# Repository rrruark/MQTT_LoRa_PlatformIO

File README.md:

# MQTT_LoRa_PlatformIO
ESP32 SX1262 LoRa to MQTT Bridge

This code is in a working state and is configured for the Heltec WiFi Lora 32 V2 Board. The only thing you need to change to get started are the WiFi and MQTT configuration parameters.

It will transmit (over LoA using an SX1262) messages posted to a MQTT topic using radio configuration parameters defined in other MQTT topics.
It will also post messages received from the SX1262 to a different MQTT topic and will re-transmit received messages allowing it to act as a repeater.

The LoRa messages are not currently compatible with The Things Network, Helium, and other commonly used LoRaWAN Internet of Shit services.

My longer term ambition is to add support for <a href="https://github.com/lora-aprs/LoRa_APRS_Tracker">LoRa APRS</a> and <a href="https://github.com/aprs434/aprs434.github.io">aprs434</a>. LoRa APRS has chosen a bandwidth and spreading factor that results in much longer transmit times than traditional AFSK1200 APRS and it does not pack messages efficiently. aprs434 proposes a more efficient packing and a higher bitrate.

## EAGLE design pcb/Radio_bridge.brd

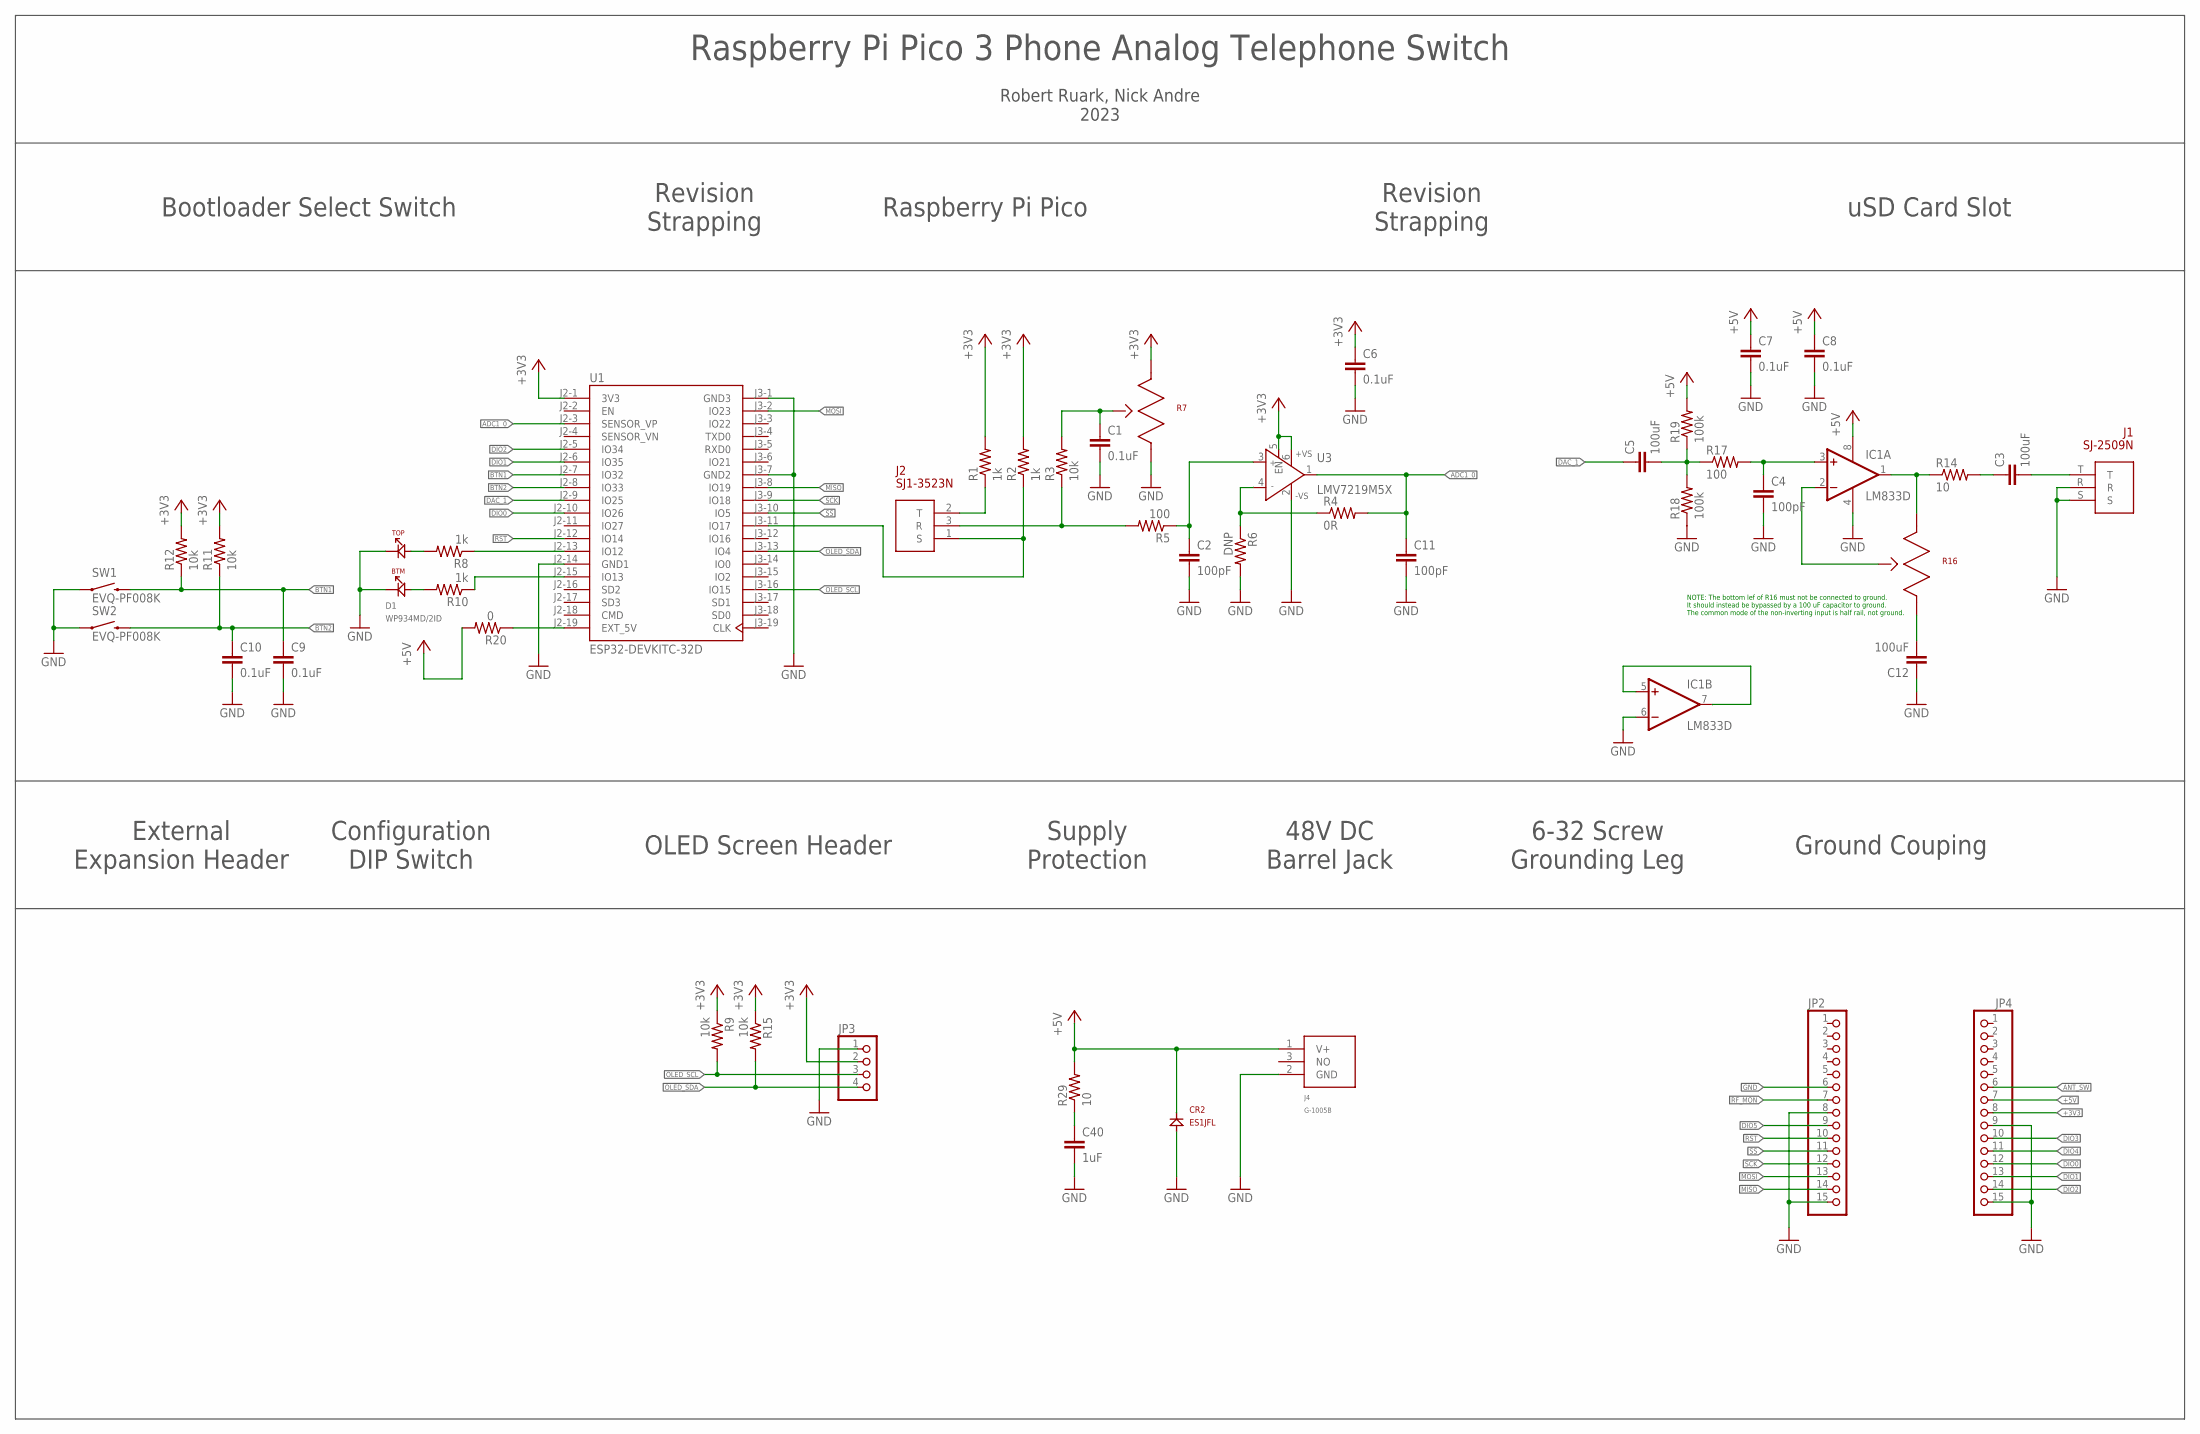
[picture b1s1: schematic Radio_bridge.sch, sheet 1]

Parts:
C1, C6, C7, C8, C9, C10: 0.1uF; 0603
C2, C4, C11: 100pF; 0603
C3, C5, C12: 100uF; 1210
C40: 1uF; 1206
CR2: ES1JFL; SOD123(AK)
D1: WP934MD/2ID
IC1: LM833D; SO08
J1: SJ-2509N; 2.5MM_TRS
J2: SJ1-3523N
J4: G-1005B
JP2, JP4: PINHD-1X15; 1X15
JP3: PINHD-1X4; 1X04
R1, R2, R8, R10: 1k; 0603
R3, R9, R11, R12, R15: 10k; 0603
R4: 0R; 0603
R5, R17: 100; 0603
R6: DNP; 0603
R7, R16: 10k; PTV09
R14: 10; 0603
R18, R19: 100k; 0603
R20: 0; 0603
R29: 10; 1206
SW1, SW2: EVQ-PF008K
U1: ESP32-DEVKITC-32D; MODULE_ESP32-DEVKITC-32D
U3: LMV7219M5X; SOT23-6

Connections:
+3V3: C6.1, JP3.2, JP4.8, R1.2, R2.2, R7.1, R9.1, R11.2, R12.2, R15.1, U1.J2-1 (3V3), U3.5 (EN), U3.6 (+VS)
+5V: C7.1, C8.1, CR2.K, IC1.8 (V+), J4.1 (V+), JP4.7, R19.2, R20.2, R29.2
ADC1_0: C11.1, R4.2, U1.J2-3 (SENSOR_VP), U3.1 (OUT)
ANT_SW: JP4.6
BTN1: C9.1, R12.1, SW1.S2 (2), U1.J2-7 (IO32)
BTN2: C10.1, R11.1, SW2.S2 (2), U1.J2-8 (IO33)
DAC_1: C5.1, U1.J2-9 (IO25)
DIO0: JP4.12, U1.J2-10 (IO26)
DIO1: JP4.13, U1.J2-6 (IO35)
DIO2: JP4.14, U1.J2-5 (IO34)
DIO3: JP4.10
DIO4: JP4.11
DIO5: JP2.9
GND: C1.2, C2.2, C4.2, C6.2, C7.2, C8.2, C9.2, C10.2, C11.2, C12.1, C40.2, CR2.A, D1.K1, D1.K2, IC1.4 (V-), IC1.6 (-IN), J1.R, J1.S, J4.2 (GND), JP2.6, JP2.8, JP2.15, JP3.1, JP4.9, JP4.15, R6.2, R7.3, R18.1, SW1.S1 (1), SW2.S1 (1), U1.J2-14 (GND1), U1.J3-1 (GND3), U1.J3-7 (GND2), U3.2 (-VS)
MIC: C2.1, R5.1, U3.3 (IN+)
MISO: JP2.14, U1.J3-8 (IO19)
MOSI: JP2.13, U1.J3-2 (IO23)
unnamed: J2.2 (T), R1.1
unnamed: C1.1, R3.2, R7.2
unnamed: R4.1, R6.1, U3.4 (IN-)
unnamed: J2.1 (S), R2.1, U1.J3-11 (IO17)
unnamed: C3.2, J1.T
unnamed: J2.3 (R), R3.1, R5.2
unnamed: D1.A2, R8.2
unnamed: D1.A1, R10.2
unnamed: R8.1, U1.J2-13 (IO12)
unnamed: R10.1, U1.J2-15 (IO13)
unnamed: C12.2, R16.3
unnamed: IC1.5 (+IN), IC1.7 (OUT)
unnamed: IC1.1 (OUT), R14.1, R16.1
unnamed: C3.1, R14.2
unnamed: IC1.2 (-IN), R16.2
unnamed: C4.1, IC1.3 (+IN), R17.2
unnamed: C5.2, R17.1, R18.2, R19.1
unnamed: R20.1, U1.J2-19 (EXT_5V)
unnamed: C40.1, R29.1
OLED_SCL: JP3.3, R9.2, U1.J3-16 (IO15)
OLED_SDA: JP3.4, R15.2, U1.J3-13 (IO4)
RF_MON: JP2.7
RST: JP2.10, U1.J2-12 (IO14)
SCK: JP2.12, U1.J3-9 (IO18)
SS: JP2.11, U1.J3-10 (IO5)

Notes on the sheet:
Raspberry Pi Pico 3 Phone Analog Telephone Switch
Robert Ruark, Nick Andre 2023
Raspberry Pi Pico
Ground Couping
External Expansion Header
OLED Screen Header
48V DC Barrel Jack
6-32 Screw Grounding Leg
Configuration DIP Switch
Supply Protection
Revision Strapping
Bootloader Select Switch
uSD Card Slot
NOTE: The bottom lef of R16 must not be connected to ground. It should instead be bypassed by a 100 uF capacitor to ground. The common mode of the non-inverting input is half rail, not ground.

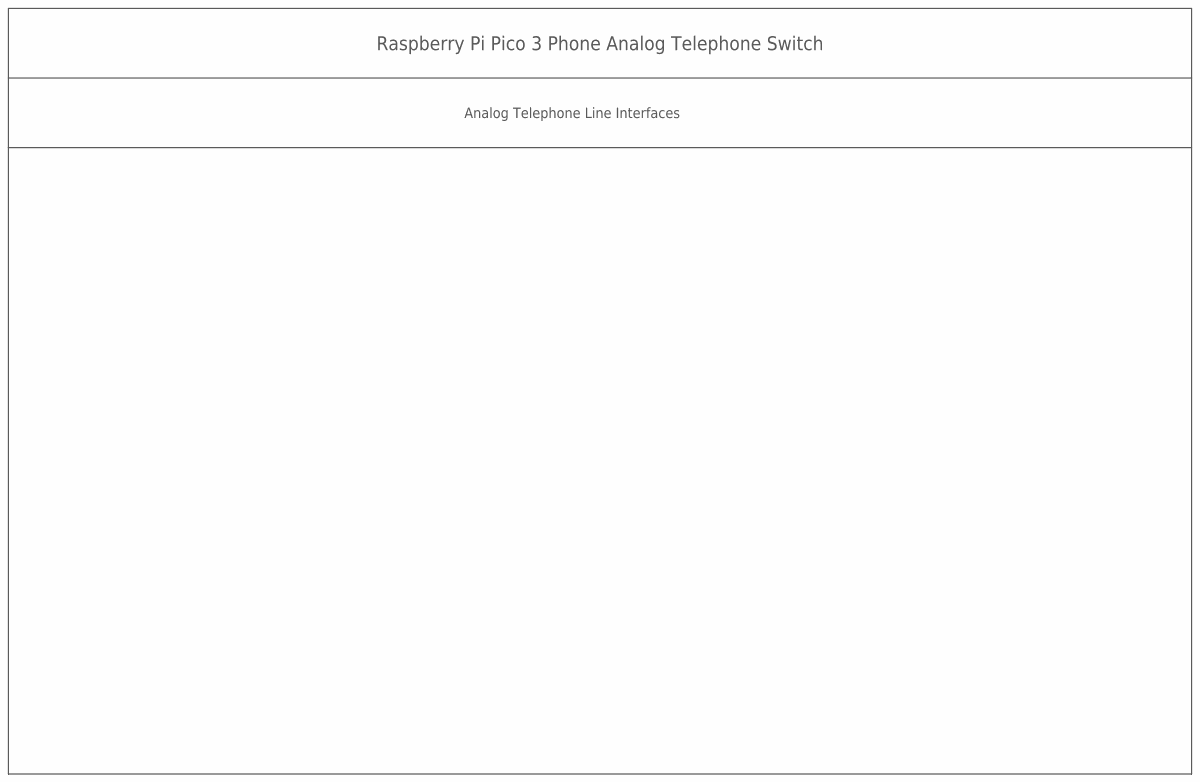
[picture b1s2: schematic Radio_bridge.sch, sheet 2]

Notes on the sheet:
Raspberry Pi Pico 3 Phone Analog Telephone Switch
Analog Telephone Line Interfaces

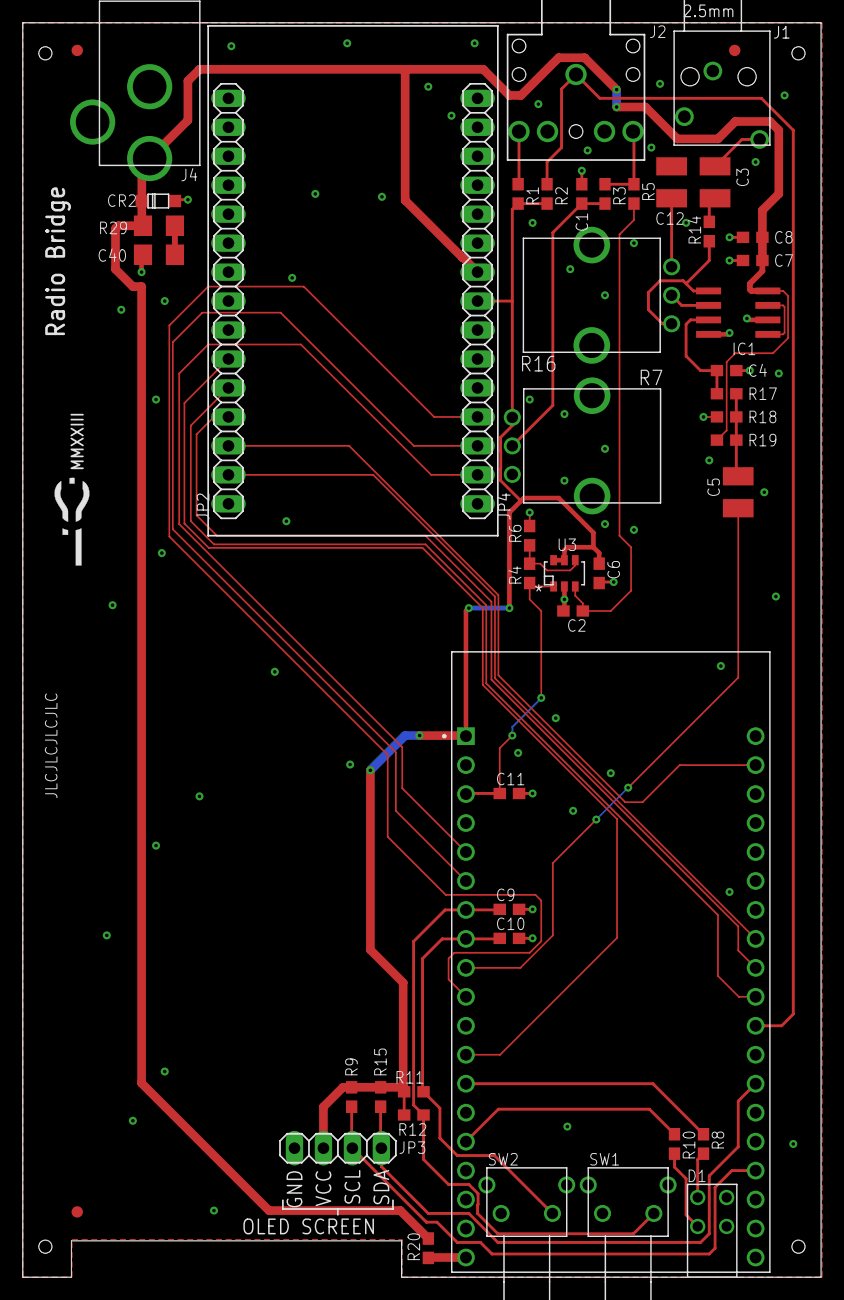
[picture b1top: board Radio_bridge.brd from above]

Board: 2 copper layers, 70.0 x 110.0 mm, 46 parts (0 on the bottom side), 37 nets.

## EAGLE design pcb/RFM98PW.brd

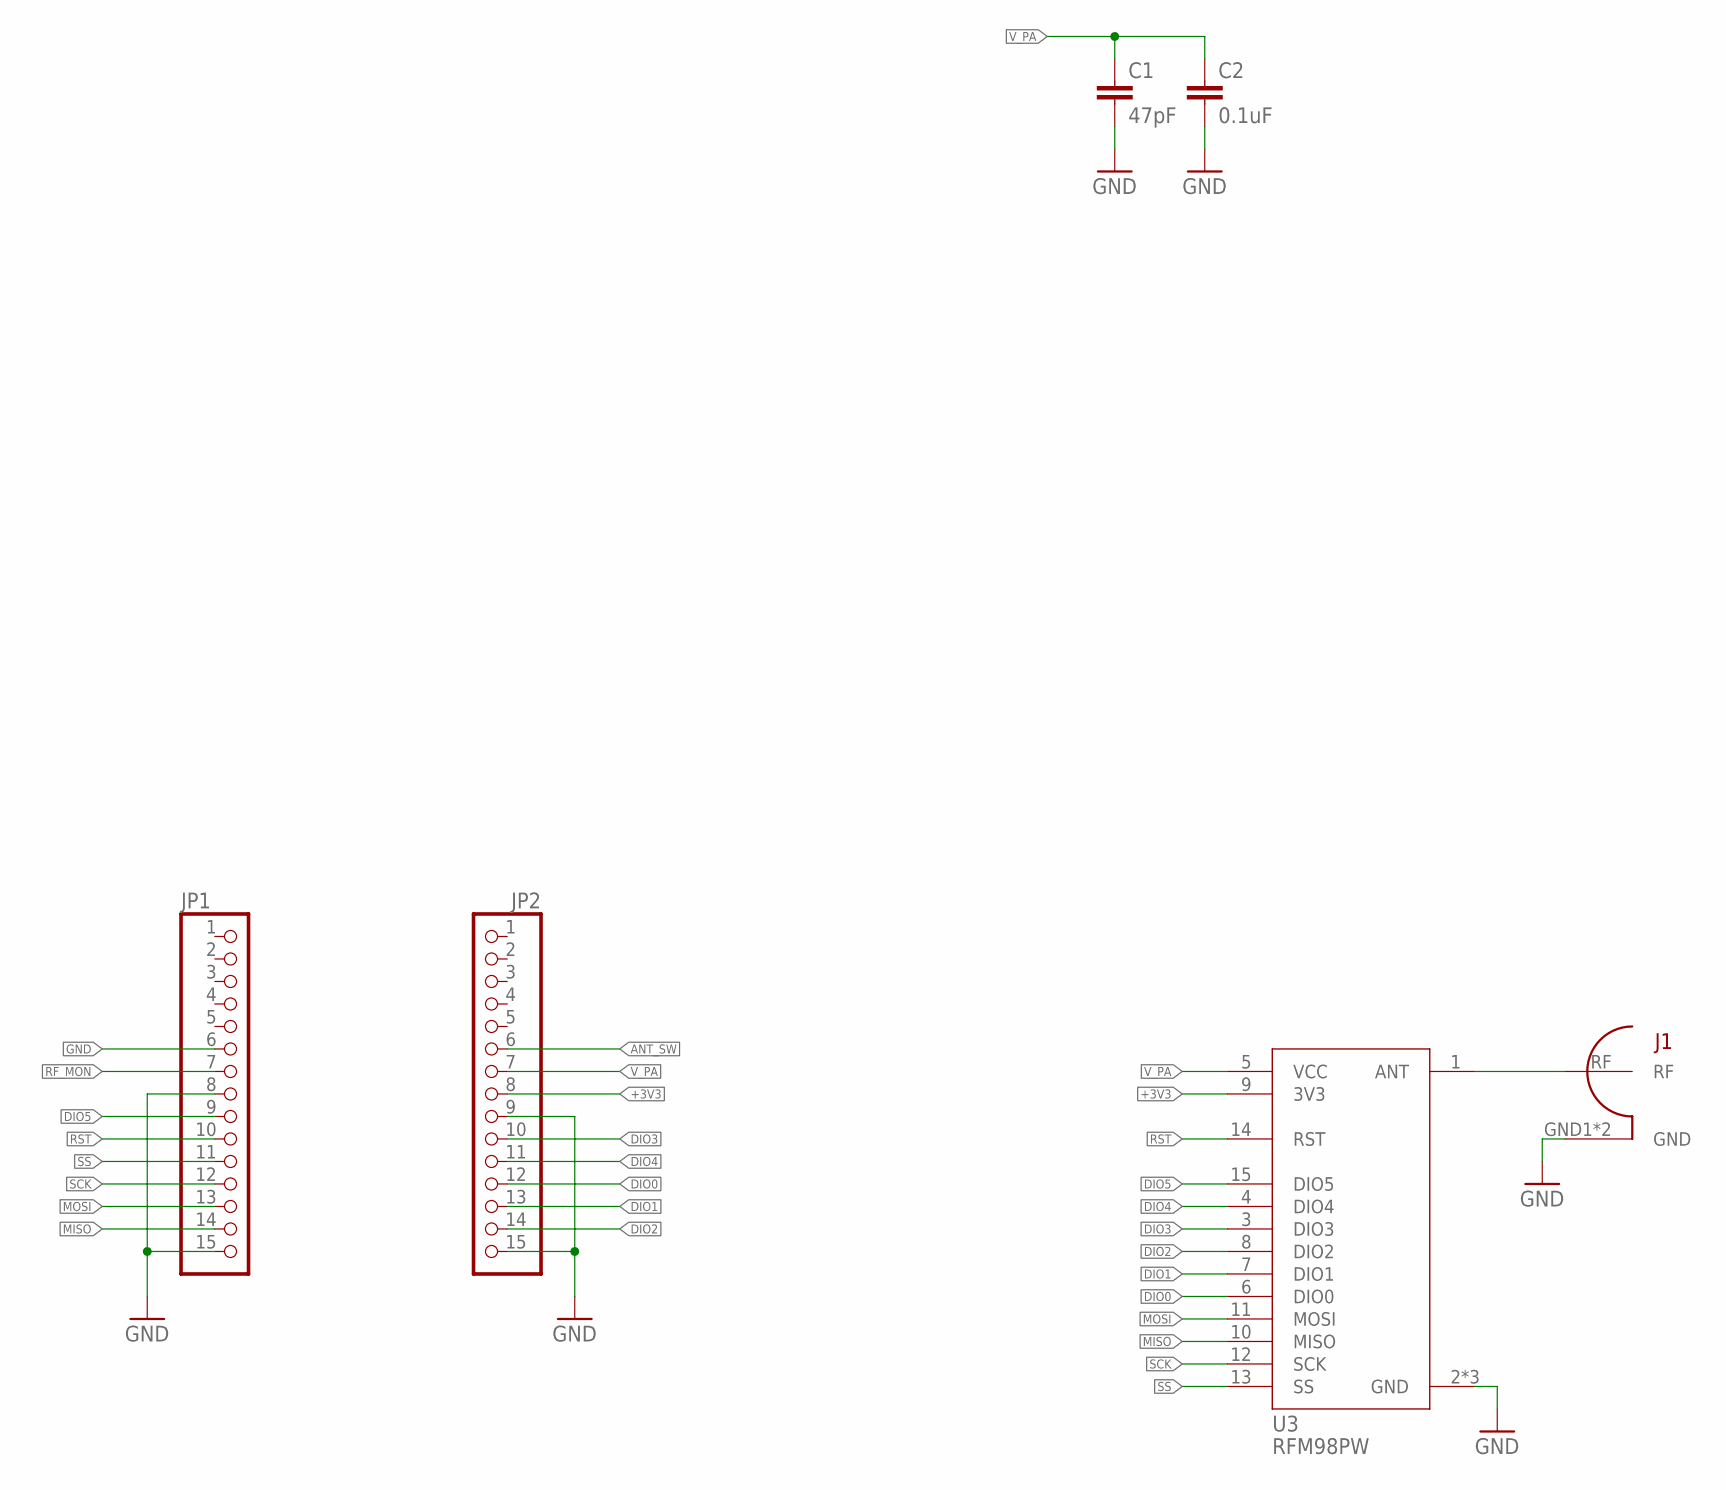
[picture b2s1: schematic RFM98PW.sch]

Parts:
C1: 47pF; 0603
C2: 0.1uF; 0603
J1: CON-SMA-EDGE-S
JP1, JP2: PINHD-1X15; 1X15
U3: RFM98PW

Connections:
+3V3: JP2.8, U3.9 (3V3)
ANT_SW: JP2.6
DIO0: JP2.12, U3.6 (DIO0)
DIO1: JP2.13, U3.7 (DIO1)
DIO2: JP2.14, U3.8 (DIO2)
DIO3: JP2.10, U3.3 (DIO3)
DIO4: JP2.11, U3.4 (DIO4)
DIO5: JP1.9, U3.15 (DIO5)
GND: C1.2, C2.2, J1.GND1 (GND), J1.GND2 (GND), JP1.6, JP1.8, JP1.15, JP2.9, JP2.15, U3.2 (GND), U3.16 (GND), U3.17 (GND)
MISO: JP1.14, U3.10 (MISO)
MOSI: JP1.13, U3.11 (MOSI)
unnamed: J1.RF, U3.1 (ANT)
RF_MON: JP1.7
RST: JP1.10, U3.14 (RST)
SCK: JP1.12, U3.12 (SCK)
SS: JP1.11, U3.13 (SS)
V_PA: C1.1, C2.1, JP2.7, U3.5 (VCC)

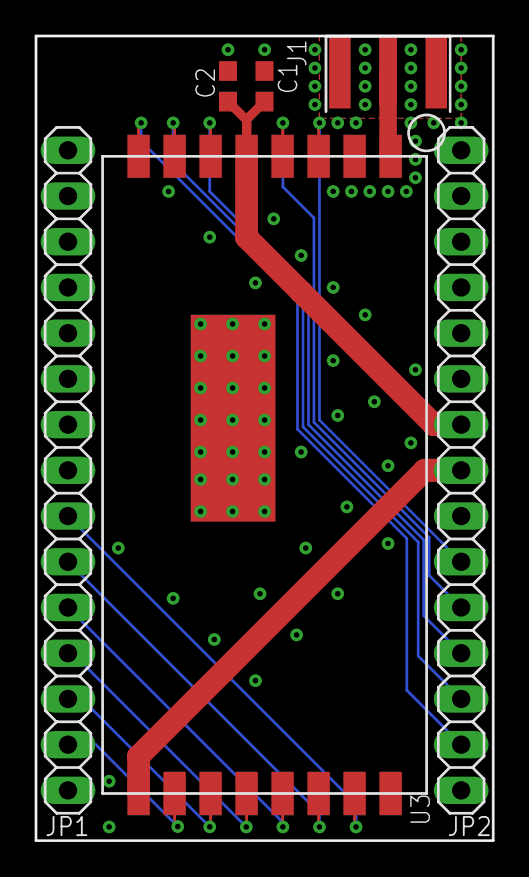
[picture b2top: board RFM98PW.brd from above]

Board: 4 copper layers, 25.4 x 44.7 mm, 6 parts (0 on the bottom side), 15 nets.

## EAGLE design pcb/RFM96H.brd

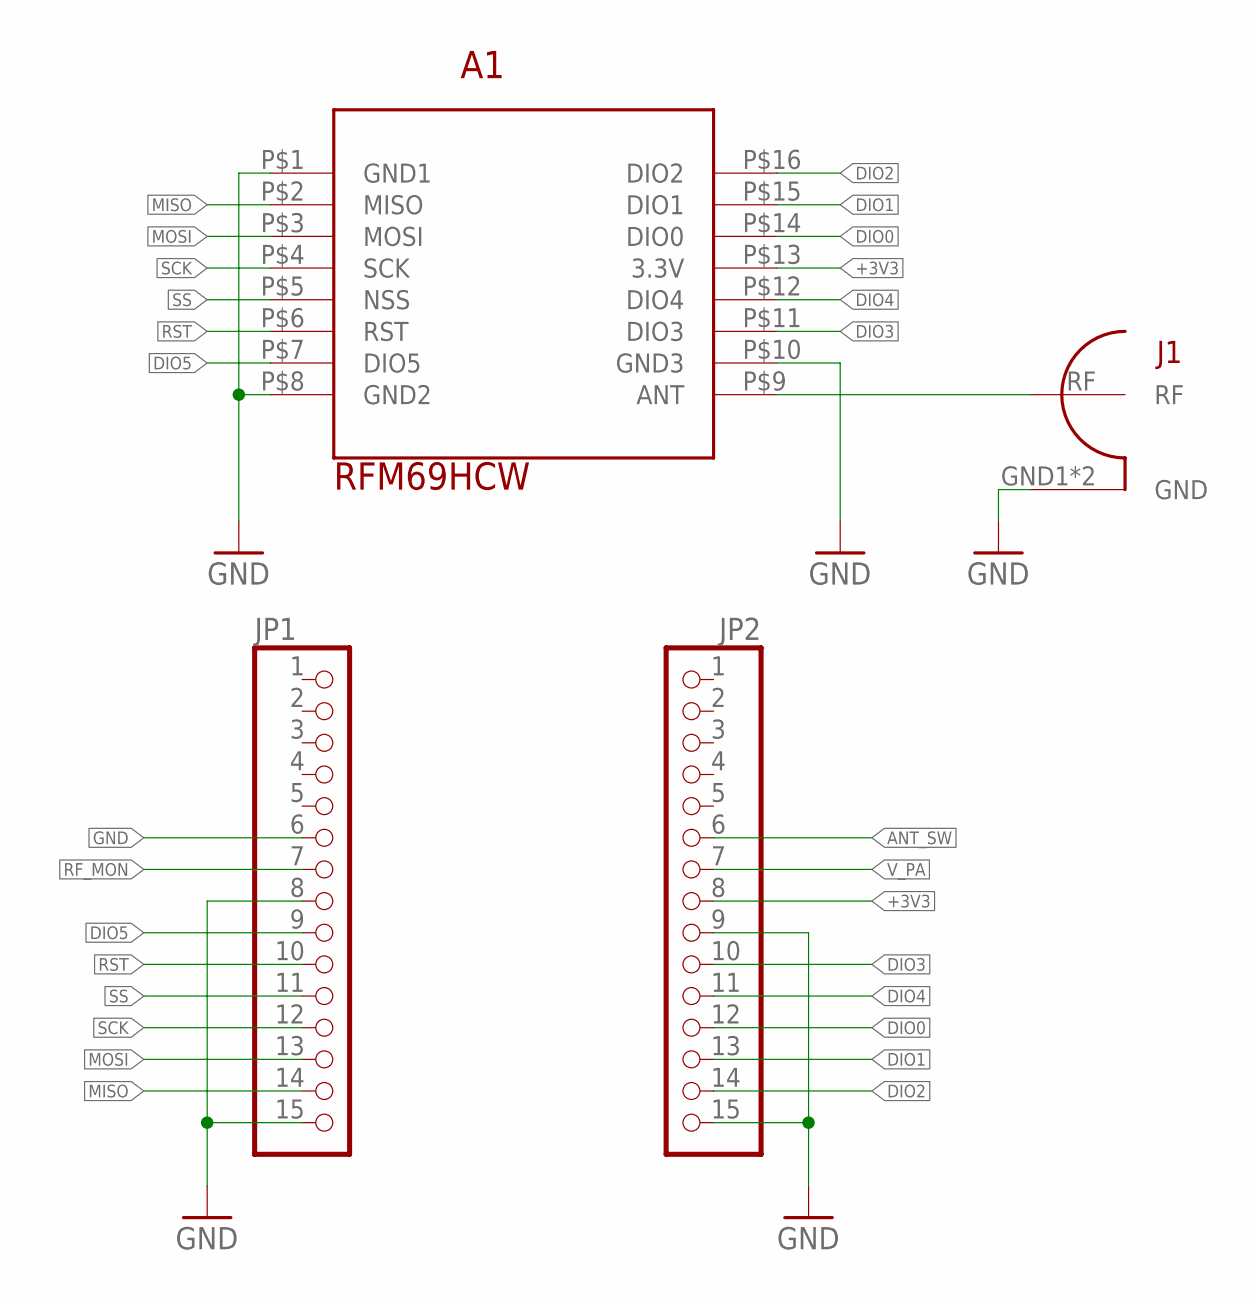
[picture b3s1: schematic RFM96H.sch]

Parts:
A1: RFM69HCW
J1: CON-SMA-EDGE-S
JP1, JP2: PINHD-1X15; 1X15

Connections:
+3V3: A1.P$13 (3.3V), JP2.8
ANT_SW: JP2.6
DIO0: A1.P$14 (DIO0), JP2.12
DIO1: A1.P$15 (DIO1), JP2.13
DIO2: A1.P$16 (DIO2), JP2.14
DIO3: A1.P$11 (DIO3), JP2.10
DIO4: A1.P$12 (DIO4), JP2.11
DIO5: A1.P$7 (DIO5), JP1.9
GND: A1.P$1 (GND1), A1.P$8 (GND2), A1.P$10 (GND3), J1.GND1 (GND), J1.GND2 (GND), JP1.6, JP1.8, JP1.15, JP2.9, JP2.15
MISO: A1.P$2 (MISO), JP1.14
MOSI: A1.P$3 (MOSI), JP1.13
unnamed: A1.P$9 (ANT), J1.RF
RF_MON: JP1.7
RST: A1.P$6 (RST), JP1.10
SCK: A1.P$4 (SCK), JP1.12
SS: A1.P$5 (NSS), JP1.11
V_PA: JP2.7

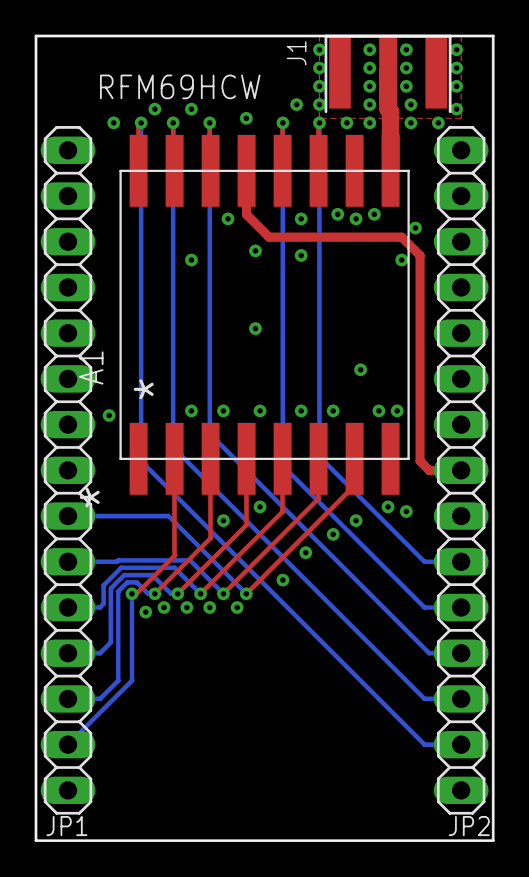
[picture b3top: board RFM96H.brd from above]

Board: 4 copper layers, 25.4 x 44.7 mm, 4 parts (0 on the bottom side), 14 nets.

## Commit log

2023-06-12 Changing to JSON for MQTT
2023-06-17 Rev2 PCB fixes
